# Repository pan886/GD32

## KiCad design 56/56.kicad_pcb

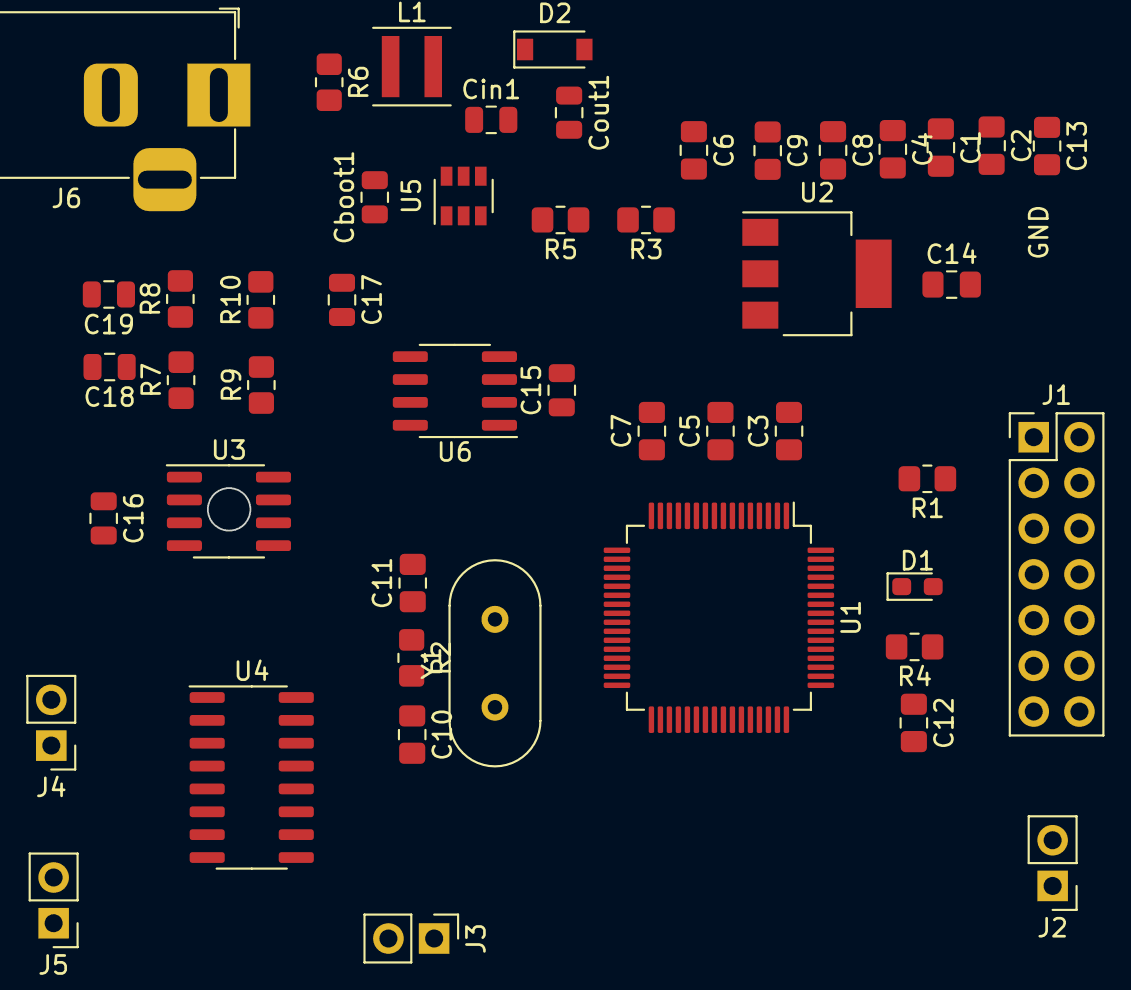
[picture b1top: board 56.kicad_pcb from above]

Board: 4 copper layers, 48 parts (0 on the bottom side), 39 nets.

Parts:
C1, C3, C7: 470pF; C_0805_2012Metric_Pad1.18x1.45mm_HandSolder
C2, C6, C9: 0.1uf; C_0805_2012Metric_Pad1.18x1.45mm_HandSolder
C4, C8: 470pf; C_0805_2012Metric_Pad1.18x1.45mm_HandSolder
C5: 330nF; C_0805_2012Metric_Pad1.18x1.45mm_HandSolder
C10, C11: 15pF; C_0805_2012Metric_Pad1.18x1.45mm_HandSolder
C12, C13: 0.1uF; C_0805_2012Metric_Pad1.18x1.45mm_HandSolder
C14: 100uF; C_0805_2012Metric_Pad1.18x1.45mm_HandSolder
C15, C16: 0.1uF; C_0805_2012Metric
C17: 4.7nF; C_0805_2012Metric
C18, C19: 100PF; C_0805_2012Metric
Cboot1: 1uF; C_0805_2012Metric
Cin1: 1-10uF; C_0805_2012Metric
Cout1: 10uF; C_0805_2012Metric
D1: LED; LED_0603_1608Metric_Pad1.05x0.95mm_HandSolder
D2: D_Schottky; D_SOD-123
J1: JTAG; PinHeader_2x07_P2.54mm_Vertical
J2, J3, J4, J5: Conn_01x02; PinHeader_1x02_P2.54mm_Vertical
J6: Barrel_Jack_Switch; BarrelJack_Horizontal
L1: L; L_Coilcraft_XxL4030
R1, R3, R5: R; R_0805_2012Metric_Pad1.20x1.40mm_HandSolder
R2: 1M; R_0805_2012Metric_Pad1.20x1.40mm_HandSolder
R4: 2k; R_0805_2012Metric_Pad1.20x1.40mm_HandSolder
R6: 100K; R_0805_2012Metric_Pad1.20x1.40mm_HandSolder
R7, R8: 61.9; R_0805_2012Metric_Pad1.20x1.40mm_HandSolder
R9, R10: 10K; R_0805_2012Metric_Pad1.20x1.40mm_HandSolder
U1: SPC560D-New_Library; TQFP-64_10x10mm_P0.5mm
U2: LM1117-3.3; SOT-223
U3: MAX31855NASA; SOIC-8_3.9x4.9mm_P1.27mm
U4: CD4052B; SOIC-16_3.9x9.9mm_P1.27mm
U5: LMR16006YQ; SOT-23-6
U6: TJA1042T; SOIC-8_3.9x4.9mm_P1.27mm
Y1: 8M; Crystal_HC49-4H_Vertical

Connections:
+3V3: C14.1, C16.2, U2.2, U2.4, U3.4
+5V: C1.1, C2.1, C4.1, C6.1, C8.1, C9.1, C12.1, C13.1, C15.2, Cout1.1, J1.11, L1.2, R3.1, R4.2, R9.1, U1.7, U1.12, U1.28, U1.34, U1.56, U2.3, U6.3
+12V: Cin1.1, J6.1, R6.1, U5.5
/CAN0HK: C18.1, R7.1, U6.7
/CAN0LK: C19.1, R8.2, U6.6
/CAN0RX: U1.15, U6.4
/CAN0TX: U1.14, U6.1
/EXTAL: C10.1, R2.2, U1.27, Y1.1
/INX: U3.3, U4.13
/INY: U3.2, U4.3
/PA5: D1.1, U1.51
/PA12: U1.22, U3.7
/PA14: U1.19, U3.5
/PA15: U1.18, U3.6
/PB10: U1.31, U4.10
/PB11: U1.38, U4.9
/RESET: J1.9, U1.9
/TCK: J1.5, R1.1
/TDI: J1.1, U1.59
/TDO: J1.3, U1.54
/TMS: J1.10, U1.53
/VDD_LV: C3.1, C5.1, C7.1, U1.11, U1.23, U1.57
/XTAL: C11.1, R2.1, U1.25, Y1.2
/x0: J2.1, U4.12
/x1: J3.1, U4.14
/x2: J4.1, U4.15
/x3: J5.1, U4.11
/y0: J2.2, U4.1
/y1: J3.2, U4.5
/y2: J4.2, U4.2
/y3: J5.2, U4.4
GND: C1.2, C2.2, C3.2, C4.2, C5.2, C6.2, C7.2, C8.2, C9.2, C10.2, C11.2, C12.2, C13.2, C14.2, C15.1, C16.1, C17.1, C18.2, C19.2, Cin1.2, Cout1.2, D2.2, J1.2, J1.4, J1.6, J1.8, J1.12, J1.14, J6.2, J6.3, R5.2, R10.2, U1.6, U1.8, U1.10, U1.24, U1.26, U1.33, U1.55, U1.58, U2.1, U3.1, U4.8, U5.2, U6.2, U6.8
unnamed: C17.2, R7.2, R8.1, R9.2, R10.1
unnamed: Cboot1.1, U5.1
unnamed: Cboot1.2, D2.1, L1.1, U5.6
unnamed: D1.2, R4.1
unnamed: R1.2, U1.60
unnamed: R3.2, R5.1, U5.3
unnamed: R6.2, U5.4

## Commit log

2021-08-02 GD32 test
2021-08-02 good
2021-08-03 drivers Please enter the commit message for your changes. Lines starting
2021-08-03 full project
2021-08-03 supend and recovery
2021-08-04 add source code
2021-08-04 时间片调度
2021-08-06 二值信号量测试
2021-08-06 计数信号量
2021-08-09 事件标志组
2021-08-09 内存申请和释放
2021-08-09 任务运行时间统计
2021-08-10 软件定时器
2021-08-11 freertos
2021-08-12 :优先级翻转
2021-08-12 互斥信号量
2021-08-13 时间管理
2021-08-16 任务通知
2021-08-16 任务通知模拟消息邮箱
2021-08-16 任务通知模拟标志事件组
2021-08-16 增加开关中断函数解析
2021-08-17 增加临界段代码的解析
2021-08-17 some comment
2021-08-17 add tasklist
2021-08-19 RT 定时器测试
2021-08-19 RT 定时器
2021-08-31 I2C DMA
2021-09-01 I2C DMA test
2021-09-03 debug timer test
2021-09-08 add some test report
2021-09-13 can test
2021-09-15 独立看门狗测试
2021-09-16 i2s dma
2021-09-18 ram to ram test
2021-09-18 # Please enter the commit message for your changes. Lines starting
2021-09-24 usart 模拟spi
2021-09-28 well
2021-09-29 dead time
2021-09-29 some commment
2021-09-30 timer DMA
2021-10-08 trigger
2021-10-08 single pluse
2021-10-09 CRC test
2021-10-11 programable resolusion
2021-10-12 DAC test
2021-10-13 noise
2021-10-14 wav test
2021-10-15 test
2021-10-19 jlink连接rvstar开发板
2021-11-19 very good
2021-12-10 tf card
